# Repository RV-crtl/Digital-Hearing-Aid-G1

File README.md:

# G1 · Standalone adaptive hearing prototype

**STM32L476RG · custom KiCad PCB · FreeRTOS · microphone / Bluetooth / induction-loop audio · physical controls**

## Start with the R26.10 code walkthrough

**[Open the four-subsystem execution guide](Documentation/SUBSYSTEMS/README.md)** — follow the real startup-to-sound runtime flow, then dive into a member's source code:

[**Anna — controls**](Documentation/SUBSYSTEMS/ANNA_CONTROLS.md) · [**Ryan — BT/telecoil**](Documentation/SUBSYSTEMS/RYAN_CONNECTIVITY.md) · [**Mariya — microphone/DSP**](Documentation/SUBSYSTEMS/MARIYA_AUDIO_DSP.md) · [**Naomi — speaker output**](Documentation/SUBSYSTEMS/NAOMI_OUTPUT.md) · [**Interface contracts**](Documentation/SUBSYSTEMS/INTERFACES.md)

Each guide starts at the event that triggers its functions, shows annotated source excerpts and exact file paths, and traces the next task, queue, interrupt, hardware or team subsystem. The [original 39-event system execution guide](Documentation/FIRMWARE_EXECUTION_GUIDE_R26.md) remains available for the full chronological walkthrough. **Documentation baseline:** latest separately delivered QR261104.10 ZIP; repository firmware sources have not yet been synchronized to that release.

The diagram above represents real interfaces and task ownership, not fictional mechanical CAD or hardware measurements.

[**Explore the interactive website**](https://rv-crtl.github.io/Digital-Hearing-Aid-G1/) · [System architecture](Documentation/PRINTABLE_SYSTEM_DIAGRAM.md) · [Black-box demonstration plan](Documentation/BLACK_BOX_TEST_PLAN.md) · [Current evidence and requirements](Documentation/G1_CURRENT_SYSTEM_REQUIREMENTS.md) · [Hardware/KiCad](Hardware/README.md)

> **Prototype, not a certified hearing aid.** This repository contains original PCB design, software source, testing infrastructure and student-team engineering work. The maximum acoustic output has not been independently calibrated for use on or in the ear. Public access is not a general reuse licence; see [publication and contributor rights](Documentation/PUBLICATION_GATE.md).

## Firmware navigation and STM32CubeIDE import

**[Read the R26 boot-to-speaker function walkthrough](Documentation/FIRMWARE_EXECUTION_GUIDE_R26.md)** — chronological annotated code excerpts, physical hardware paths, per-source DSP functions, peripheral drivers, source routing, FreeRTOS tasks, speaker FIFO, diagnostics, and exact `Core/Src/` locations.

To download a **firmware-only ZIP from GitHub**, open [Actions → Export clean STM32CubeIDE project](../../actions/workflows/cubeide-clean-export.yml), choose **Run workflow**, and download the `STM32CubeIDE-clean-project` artifact from the completed run. Alternatively run `Tools/Export-CubeIDE.ps1 -OutputPath dist` in PowerShell from the repository checkout. These exports reflect the **repository revision being built**, not the separate QR261104.8 ZIP until the source-sync issue below is resolved.

For a source checkout, use **File → Import → Existing Projects into Workspace** and select the repository root containing `.project` and `.cproject`; do not import a historical reference firmware as a second project. The active application entry point is **`Core/Src/main.c`**, and the development configuration is described by the root `.ioc`. Commit history retains deleted recovery/prototype files if historical investigation is needed.

**Release synchronization:** to publish the supplied QR261104.8 ZIP into a local Git clone safely, use [`Tools/Sync-FirmwareRelease.ps1`](Tools/Sync-FirmwareRelease.ps1). Run it first with `-ZipPath <path-to-ZIP>` for validation and again with `-Apply` to replace the active firmware, create a Git commit and push to `main`. It requires a clean clone and your existing GitHub Git credentials. The QR261104.8 clean firmware archive distributed separately contains newer telecoil modules than the current repository revision. This repository should not be represented as the exact QR261104.8 release until its source and `.ioc` are synchronized and a native CubeIDE build passes. The guide describes QR261104.8 and marks differences where relevant.

## The real prototype

The physical target is a **standalone custom PCB**, not a Nucleo board. A ST-LINK is needed only for programming and optional engineering diagnosis, not for intended normal operation. The hardware incorporates an STM32L476RG, digital PDM microphone, MPR121 capacitive touch, rotary encoder, Bluetooth audio, a telecoil input with PCM1808 conversion, FreeRTOS and a speaker/audio-output chain. The bench-tested R24 firmware was reported to operate without Nucleo after a wiring issue was resolved.

The team subsequently developed **R26** with higher-sensitivity ambient audio, telecoil idle-noise reduction, adaptive gain, and incremental acoustic feature clustering. **R26 firmware is a candidate, not a confirmed on-PCB acceptance result.**

| Function | Evidence currently available | Important qualification |
| --- | --- | --- |
| Microphone → speaker | Operator-confirmed in R24; R26 DSP host tests | Distant pickup, distortion, safe SPL and ambient balance need measurement |
| Bluetooth → speaker | Operator-confirmed in R24 | Bluetooth module and source output remain subject to demonstration checks |
| Telecoil → speaker | Operator-confirmed with **PCM LOW16** and **FILTER ON** | Residual analogue hiss/weak-signal behaviour needs listening and bench measurements |
| MPR121 touch / encoder | Operator-confirmed, R21 control regression tests | Repeatability and user-response timing remain black-box criteria |
| Untethered USB-C power | R24 operator-confirmed after resolving external wiring | Battery source/protection/charging cannot be inferred from this result |
| Adaptive scene model | R26 portable C tests | **Three unsupervised clusters**, not a pretrained speech/car/pedestrian classifier |
| FreeRTOS / DMA | Static contracts and host tests | Final CPU load, timing, interrupts, underruns and SRAM headroom need recorded board evidence |

## Important: two firmware baselines

**Do not flash the root CubeIDE project assuming it is R26.** The root files currently include an earlier Nucleo-oriented group source baseline, augmented with portable R20–R26 DSP/control improvements. R26's complete custom-PCB project was distributed separately; a clean, native STM32CubeIDE 1.19.0 GCC build and intentional whole-project promotion are required before declaring it this repository's authoritative firmware. The runtime should not be assembled by casually combining half of one firmware revision with the other.

See [firmware integration and source ownership](Documentation/G1_CURRENT_SYSTEM_REQUIREMENTS.md) and [integration issue #27](https://github.com/RV-crtl/Digital-Hearing-Aid-G1/issues/27).

## Interactive engineering site

The [site](https://rv-crtl.github.io/Digital-Hearing-Aid-G1/) provides an interactive CAD explorer (3MF/GLB with local upload), source-linked **original KiCad schematics**, signal paths and task ownership, code references, and a demonstration checklist. All files under `Hardware/Original_KiCad/` remain unchanged.

The uploaded **November 2026 full multi-body assembly** contains 1,713 3MF mesh objects (460,021 triangles), including PCB, housing and separated structures. The *previous* 3MF stored at `docs/assets/g1-assembly.3mf` is an earlier revision. The newest upload can be opened through the site's **Open your 3D CAD** control without sending it to a server; its full binary is not yet tracked on GitHub. See [CAD provenance and viewing guide](Documentation/CAD_ASSEMBLY_AND_VIEWERS.md).

## Project navigation

| Area | Start here |
| --- | --- |
| Software / RTOS | [Core source](Core/Src) · [source ownership map](Documentation/CODE_MAP.md) |
| DSP and adaptive learning | [Ambient DSP](Core/Src/g1_ambient_dsp.c) · [online clusters](Core/Src/g1_scene_ml.c) · [telecoil cleanup](Core/Src/tc_cleanup.c) |
| Circuits / layout | [Original KiCad files](Hardware/Original_KiCad) · [hardware notes](Hardware/README.md) |
| Firmware import | [CubeIDE procedure](Documentation/GROUP_G1_IMPORT_AND_BUILD.md) · [R26 integration gate](https://github.com/RV-crtl/Digital-Hearing-Aid-G1/issues/27) |
| Demonstration | [System diagram](Documentation/PRINTABLE_SYSTEM_DIAGRAM.md) · [current requirements](Documentation/G1_CURRENT_SYSTEM_REQUIREMENTS.md) · [20-minute black-box test](Documentation/BLACK_BOX_TEST_PLAN.md) |
| Validation / CI | [Host validation](Validation/README.md) · [Actions](https://github.com/RV-crtl/Digital-Hearing-Aid-G1/actions) |
| Contributors / release | [CONTRIBUTING](CONTRIBUTING.md) · [SECURITY](SECURITY.md) · [publication gate](Documentation/PUBLICATION_GATE.md) |

## Working practices

Run `python3 Validation/run_host_validation.py`, `python3 docs/validate_site.py` and the relevant portable C tests before submitting a PR. **Green source-level CI does not mean ARM firmware compiled, a device booted, or acoustic performance was measured.** The correct demonstration image must start from its intended regulated power supply with ST-LINK and diagnostics disconnected; no synthetic stress/demo tasks should be enabled for operating mode.

Earlier G2/G3/G5/G11 and R-series materials remain in `Documentation/` for traceability, but **the current requirements and black-box plan linked above supersede their historical demonstration descriptions.** Avoid presenting historical statements about an unintegrated mic, Nucleo B1, or simulated user controls as the current PCB's features.

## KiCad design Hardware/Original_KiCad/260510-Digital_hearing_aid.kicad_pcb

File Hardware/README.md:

# KiCad electrical hardware — actual supplied group design

Open [`Original_KiCad/260510-Digital_hearing_aid.kicad_pro`](Original_KiCad/260510-Digital_hearing_aid.kicad_pro) using KiCad's **Project Manager** (rather than separately opening the board and schematics). PCB and hierarchical schematic pages are included. The board is **NOT validated/fabrication-approved** by inclusion in GitHub.

## Critical editing dependency

`fp-lib-table` and `sym-lib-table` reference numerous `${KIPRJMOD}/...` third-party symbol and footprint library folders. Several were supplied in the original group design ZIP but were not copied into this code repository. KiCad can often *view* embedded schematic symbol and PCB footprint representations, but library reassignment and full schematic/PCB editing may fail. Obtain the group's original `260802-Digital_hearing_aid_w_PCB` archive and copy only approved/licensed dependencies into `Hardware/Original_KiCad/`, preserving relative paths. Keep vendor library notices and provenance. Do **not** commit the original archive's `.git`, `.history`, caches, thousands of unrelated components or unreviewed third-party binaries.

Run:

```bash
python3 Validation/python/audit_kicad.py
```

It enumerates unresolved library path references, project/schematic presence and basic PCB object counts. **It does not run KiCad ERC or DRC**.

## Actual required electrical checks

1. Confirm net/pin assignment using [`STM32_U13_PINMAP.csv`](STM32_U13_PINMAP.csv) and the schematic, especially different STM32 peripheral alternate functions compared with the Nucleo firmware.
2. Run KiCad schematic ERC and PCB DRC in a compatible KiCad installation and attach *unedited reports* with the tool version and rule configuration.
3. Verify power input path / source selection, regulated rails, analogue ground, USB-C CC resistors, ESD, debug connector, HSE, BOOT0 and RESET.
4. Confirm the unconnected MPR121 address/IRQ and encoder push contacts. Don't claim these work without design corrections and testing.
5. Check that no 2-cell LiFePO4 charge/balance stage is falsely implied by the USB-C connector.
6. Fabricate only after manufacturer stack-up checks, Gerber review, DFM and real continuity/power-up tests.

For the risk and peripheral porting checklist see [`CUSTOM_PCB_PORTING_CHECKLIST.md`](CUSTOM_PCB_PORTING_CHECKLIST.md).

## G11 intended operating supply and standalone target

The team specifies **two 26650 LiFePO4 3.25 V nominal cells in series** (6.50 V nominal). This value is the **battery pack**, not the MCU supply rail: trace the actual cell balancing/protection, current limiting, low-voltage cutoff, buck/LDO conversion and acoustic output stages before operating. The final demonstrator is the custom PCB alone: it must not depend on a Nucleo, debug dongle, PC or serial console. The team reports physical hardware operational, but a specific firmware SHA/PCB revision/end-to-end black-box test record is not attached here. See [G11 custom-PCB bring-up plan](../Documentation/G11_STANDALONE_CUSTOM_PCB_RELEASE_PLAN.md).

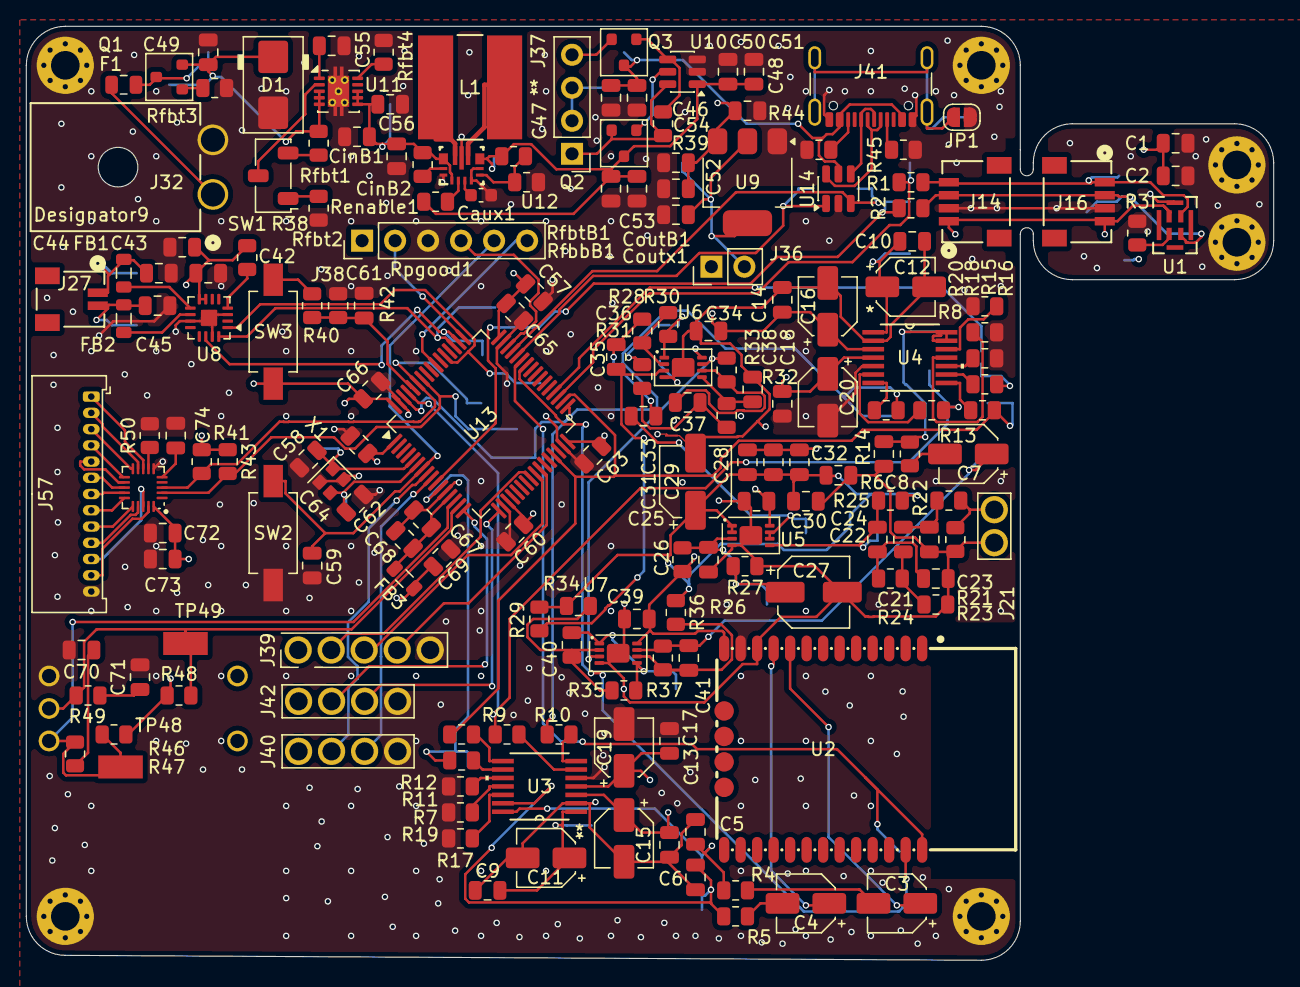
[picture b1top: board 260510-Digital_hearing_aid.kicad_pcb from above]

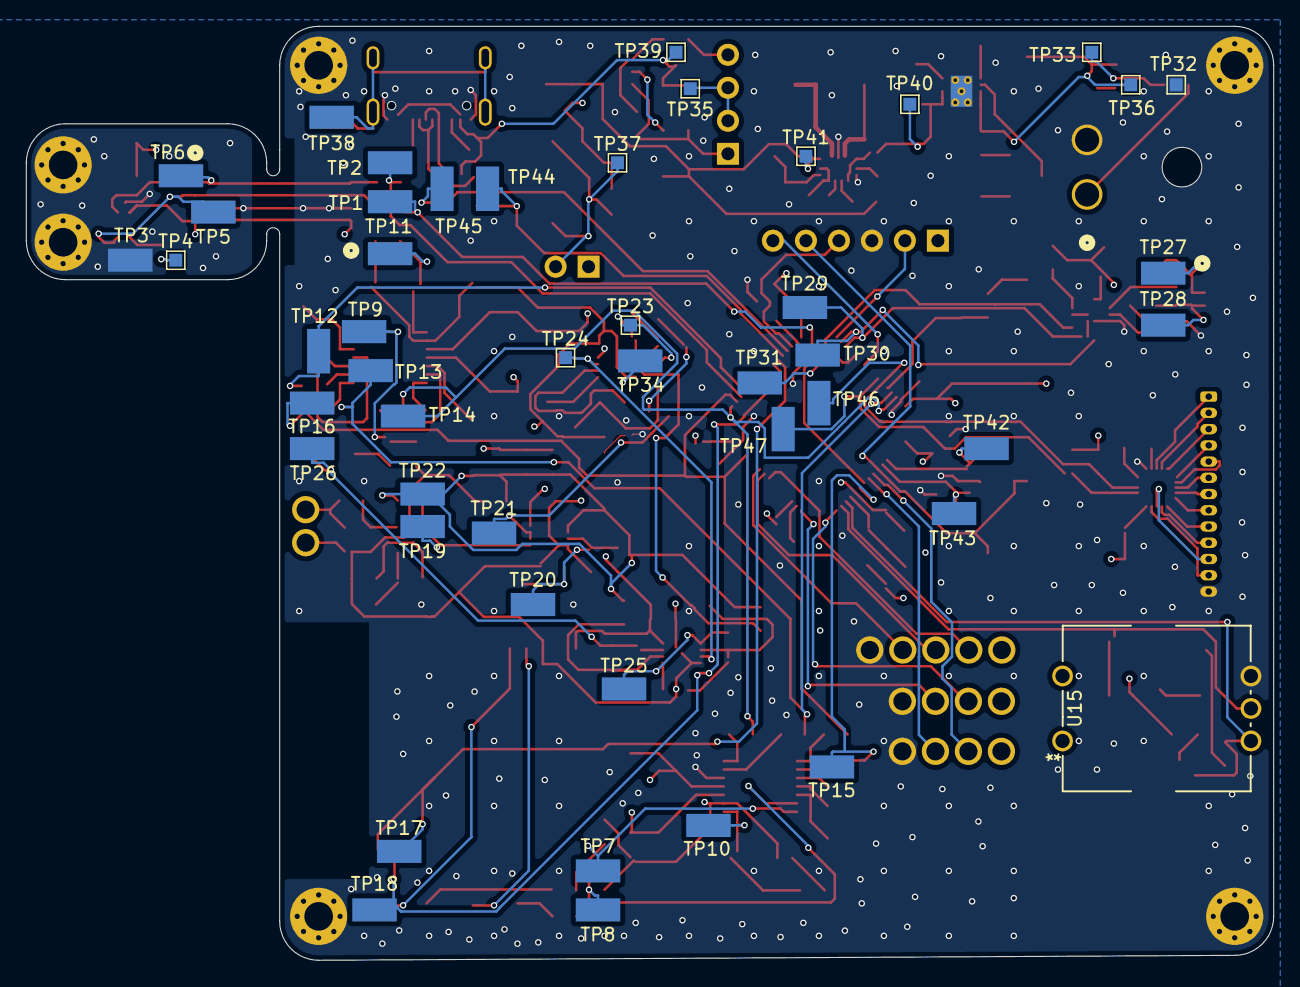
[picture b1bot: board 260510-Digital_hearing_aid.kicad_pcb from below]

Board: 4 copper layers, 96.0 x 71.9 mm, 236 parts (48 on the bottom side), 134 nets.

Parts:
C1, C42, C46, C50, C57: 10u; C_0805_2012Metric
C2, C9, C10, C13, C14, C17, C18, C25, C26, C28, C30, C31, C32, C33, C34, C39, C43, C47, C49, C51, C54, C59, C60, C61, C63, C64, C65, C66, C72, C73, C74: 100n; C_0805_2012Metric
C3, C4, C7, C11, C12, C15, C16, C19, C20: 10u; CP_Elec_4x5.3
C5, C6, C8: 100p; C_0805_2012Metric
C21, C44, C45: 470p; C_0805_2012Metric
C22: 33n; C_0805_2012Metric
C23, C55: 1n; C_0805_2012Metric
C24, C56, C68, C69: 1u; C_0805_2012Metric
C27, C29: 10u; CP_Elec_5x5.7
C35, C36: 22n; C_0805_2012Metric
C37: 3n; C_0805_2012Metric
C38: 1n5; C_0805_2012Metric
C40, C41: 22p; C_0805_2012Metric
C48, C52: 22u; C_0805_2012Metric
C53: 47u; C_0805_2012Metric
C58, C62: 10p; C_0805_2012Metric
C67, C70, C71: 10n; C_0805_2012Metric
Caux1: 100n; C_0603_1608Metric
CinB1, CinB2: 22u; C_0805_2012Metric
CoutB1: 22u; C_0805_2012Metric
Coutx1: 10u; C_0805_2012Metric
D1: SMBJ8.0A; D_SMB
F1: Fuse; Fuse_0805_2012Metric
FB1, FB2, FB3: 120R @100MHz; L_0805_2012Metric
H1, H2, H3, H4, H5, H6: MountingHole_Pad; MountingHole_2.2mm_M2_Pad_Via
J14, J16: Microphone Connectors; CONN_SM04B-SRSS-TB_JST
J21: Telecoil; PinHeader_01x02_P2.54mm_Vertical_THT_D1.4mm
J27: Bone Conductor Connector; CONN_SM02B-SRSS-TB_JST
J32: 1726480102; CONN_SD-172648-0000_02_MOL
J36: Conn_01x02_Pin; PinHeader_1x02_P2.54mm_Vertical
J37: Conn_01x04_Pin; PinHeader_1x04_P2.54mm_Vertical
J38: ST_LINK; PinHeader_1x06_P2.54mm_Vertical
J39: Number of Lines; PinHeader_01x05_P2.54mm_Vertical_THT_D1.4mm
J40, J42: Impedance @ Frequency; PinHeader_01x04_P2.54mm_Vertical_THT_D1.4mm
J41: USB_C_Receptacle_USB2.0_16P; USB_C_Receptacle_GCT_USB4105-xx-A_16P_TopMnt_Horizontal
J57: Conn_01x13; Molex_PicoBlade_53048-1310_1x13_P1.25mm_Horizontal
JP1: SolderJumper_2_Open; SolderJumper-2_P1.3mm_Open_RoundedPad1.0x1.5mm
L1: 1u5; IND_BOURNS_SDR0805
NT1: NetTie_2; Net_Tie_0.16mm_6mil
Q1, Q2, Q3: AO3419; SOT-23
R1, R2, R30, R33: 33R; R_0805_2012Metric
R3, R4, R5, R6, R7, R8, R17, R18, R19, R20, R24, R34, R36, R40, R41, R43, R46, R47, R48, R49: 10k; R_0805_2012Metric
R9, R10, R11, R12, R13, R14, R15, R16: 100R; R_0805_2012Metric
R21, R25, R38: 100k; R_0805_2012Metric
R22: 1k; R_0805_2012Metric
R23, R35, R37: 47k; R_0805_2012Metric
R26, R27: 22k; R_0805_2012Metric
R28: 21k5; R_0805_2012Metric
R29: 43k; R_0805_2012Metric
R31, R32: 11k7; R_0805_2012Metric
R39: 470k; R_0805_2012Metric
R42: 220R; R_0805_2012Metric
R44, R45: 5k1; R_0805_2012Metric
R50: 75k; R_0805_2012Metric
Renable1: 10k; R_0805_2012Metric
RfbbB1: 100k; R_0805_2012Metric
Rfbt1: 301k; R_0805_2012Metric
Rfbt2, Rfbt3: 100k; R_0805_2012Metric
Rfbt4: 45k3; R_0805_2012Metric
RfbtB1: 523k; R_0805_2012Metric
Rpgood1: 100k; R_0805_2012Metric
SW1: SW_Nidec_CAS-120TA; Nidec_Copal_CAS-120A
SW2, SW3: Switch_Tactile_CnK; Button_CnK_PTS636.0_6x3.5mm
TP1: MicClk1; KEYSTONE_5015
TP2: MicSd1; KEYSTONE_5015
TP3: GND1; KEYSTONE_5015
TP4: Ext3V0; TestPoint_Pad_1.0x1.0mm
TP5: MicClk2; KEYSTONE_5015
TP6: MicSd2; KEYSTONE_5015
TP7: VinR1; KEYSTONE_5015
TP8: VinL1; KEYSTONE_5015
TP9: TcVin1; KEYSTONE_5015
TP10: BtVref_adc1; KEYSTONE_5015
TP11: TcVref_adc1; KEYSTONE_5015
TP12: Sai2SD1; KEYSTONE_5015
TP13: SaiMCLK1; KEYSTONE_5015
TP14: SaiFS1; KEYSTONE_5015
TP15: SaiSD1; KEYSTONE_5015
TP16: SaiSCK1; KEYSTONE_5015
TP17: BtRx1; KEYSTONE_5015
TP18: BtTx1; KEYSTONE_5015
TP19: BuffIn1; KEYSTONE_5015
TP20: Buff+1; KEYSTONE_5015
TP21: BuffOut1; KEYSTONE_5015
TP22: TcVref1; KEYSTONE_5015
TP23: FiltIn1; TestPoint_Pad_1.0x1.0mm
TP24: FiltOut1; TestPoint_Pad_1.0x1.0mm
TP25: TcAmpIn1; KEYSTONE_5015
TP26: TcAmpOut1; KEYSTONE_5015
TP27: Spk+1; KEYSTONE_5015
TP28: Spk-1; KEYSTONE_5015
TP29: SpkCK1; KEYSTONE_5015
TP30: SpkFS1; KEYSTONE_5015
TP31: SpkSD1; KEYSTONE_5015
TP32: BATT-; TestPoint_Pad_1.0x1.0mm
TP33: BATT+; TestPoint_Pad_1.0x1.0mm
TP34: GndA1; KEYSTONE_5015
TP35: 5V; TestPoint_Pad_1.0x1.0mm
TP36: TpsVin1; TestPoint_Pad_1.0x1.0mm
TP37: 3V0; TestPoint_Pad_1.0x1.0mm
TP38: ChassGnd1; KEYSTONE_5015
TP39: VBus1; TestPoint_Pad_1.0x1.0mm
TP40: TpsOut1; TestPoint_Pad_1.0x1.0mm
TP41: BATT5V+1; TestPoint_Pad_1.0x1.0mm
TP42: HseIN1; KEYSTONE_5015
TP43: HseOUT1; KEYSTONE_5015
TP44: UsbD-1; KEYSTONE_5015
TP45: UsbD+1; KEYSTONE_5015
TP46: CaptoSDA1; KEYSTONE_5015
TP47: CaptoSCL1; KEYSTONE_5015
TP48: EncA1; KEYSTONE_5015
TP49: EncB1; KEYSTONE_5015
U1: MP34DT05TR-A; MP34DT05TR-A_STM
U2: DFR0781; COMM-SMD_L23.0-W15.5-P1.27_DFR0781
U3, U4: PCM1808PWR; PW14
U5, U6, U7: MCP6232T-E-MNY; DFN-8-1EP_3x2mm_P0.5mm_EP1.75x1.45mm
U8: MAX98357A; TQFN-16-1EP_3x3mm_P0.5mm_EP1.23x1.23mm
U9: AMS1117-3.3; SOT-223-3_TabPin2
U10: LTC4412ES6#TRMPBF; TSOT-23-6
U11: TPS259260DRCR; VSON-10_Custom
U12: TPS63070RNMR; RNM0015A
U13: STM32L476RGTx; LQFP-64_10x10mm_P0.5mm
U14: USBLC6-2SC6; SOT-23-6
U15: PEC11R-4215F-S0024; TO_215F-S0024
U16: MPR121QR2; QFN-20_3x3mm_P0.4mm
X1: 16MHz; Crystal_SMD_SeikoEpson_FA128-4Pin_2.0x1.6mm

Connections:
3.3V_A: C67.1, C68.1, FB3.1, U13.13 (VDDA)
+3V3: C1.1, C2.1, C17.1, C18.1, C19.1, C20.1, C57.1, C60.1, C63.1, C64.1, C65.1, C66.1, C69.1, C72.1, C73.2, FB3.2, J14.1, J16.4, J36.1, J38.1, J39.1, J40.1, J42.1, R41.1, R43.1, SW3.2, TP4.1 (1_1), U1.1 (VDD), U3.4 (VDD), U4.4 (VDD), U13.1 (VBAT), U13.19 (VDD), U13.32 (VDD), U13.48 (VDDUSB), U13.64 (VDD), U16.20 (VDD)
+5V: C13.1, C14.1, C15.1, C16.1, C25.1, C34.1, C39.1, C42.1, C43.1, C48.2, C53.1, C54.2, J37.2, J37.3, R26.2, R38.1, R46.1, R48.1, TP35.1 (1_1), U2.13 (VCC), U3.3 (VCC), U4.3 (VCC), U5.8 (V+), U6.8 (V+), U7.8 (V+), U8.7 (VDD), U8.8 (VDD), U9.3 (VI)
+5VBAT: C50.1, C51.2, CoutB1.1, Coutx1.1, Q2.3 (D), RfbtB1.1, Rpgood1.1, TP41.1 (1_1), U10.1 (VIN), U12.7 (VOUT), U12.8 (VOUT)
/Control, Connectivity, and Power/Audio Input/DFSDM_CLK: J14.3, J16.2, R2.2, TP5.TP, U1.3 (CLK)
/Control, Connectivity, and Power/Audio Input/DFSDM_DOUT: J14.4, J16.1, R1.2, TP6.TP, U1.4 (DOUT)
/Control, Connectivity, and Power/Audio Input/DFSDM_MIC.CKOUT: R2.1, TP1.TP, U13.10 (DFSDM1_CKOUT)
/Control, Connectivity, and Power/Audio Input/DFSDM_MIC.SD: R1.1, TP2.TP, U13.35 (DFSDM1_DATIN2)
/Control, Connectivity, and Power/Connectivity/Analog Frontend/Active Bandpass 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: C35.1, TP21.TP, U5.6 (-), U5.7
/Control, Connectivity, and Power/Connectivity/Analog Frontend/Active Bandpass 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: R33.1, TP24.1 (1_1), U6.7, U7.3 (+)
/Control, Connectivity, and Power/Connectivity/Analog Frontend/TC+: J21.1, R21.2, R22.2
/Control, Connectivity, and Power/Connectivity/Analog Frontend/TC_DACO: C7.1, C41.2, R37.2, TP26.TP, U7.7
/Control, Connectivity, and Power/Connectivity/Analog Frontend/Telecoil Buffer 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: C24.2, R25.2, TP19.TP, U5.5 (+)
/Control, Connectivity, and Power/Connectivity/BT_BCK: R12.1, U3.8 (BCK)
/Control, Connectivity, and Power/Connectivity/BT_DACL: C4.1, U2.10 (DACL)
/Control, Connectivity, and Power/Connectivity/BT_DACR: C3.1, U2.9 (DACR)
/Control, Connectivity, and Power/Connectivity/BT_DOUT: R11.1, U3.9 (DOUT)
/Control, Connectivity, and Power/Connectivity/BT_FMT: R17.1, U3.12 (FMT)
/Control, Connectivity, and Power/Connectivity/BT_LRCK: R10.1, U3.7 (LRCK)
/Control, Connectivity, and Power/Connectivity/BT_MD0: R7.1, U3.10 (MD0)
/Control, Connectivity, and Power/Connectivity/BT_MD1: R19.1, U3.11 (MD1)
/Control, Connectivity, and Power/Connectivity/BT_SCKI: R9.1, U3.6 (SCKI)
/Control, Connectivity, and Power/Connectivity/BT_VINL: C6.1, R5.2, TP8.TP, U3.13 (VINL)
/Control, Connectivity, and Power/Connectivity/BT_VINR: C5.1, R4.2, TP7.TP, U3.14 (VINR)
/Control, Connectivity, and Power/Connectivity/BT_VREF: C9.1, C11.1, TP10.TP, U3.1 (VREF)
/Control, Connectivity, and Power/Connectivity/SAI1A_CONN.FS: R10.2, R14.2, TP14.TP, U13.33 (SAI2_FS_A), U13.62 (SAI1_FS_A)
/Control, Connectivity, and Power/Connectivity/SAI1A_CONN.MCLK: R9.2, R13.2, TP13.TP, U13.61 (SAI1_MCLK_A)
/Control, Connectivity, and Power/Connectivity/SAI1A_CONN.SCK: R12.2, R16.2, TP16.TP, U13.29 (SAI1_SCK_A), U13.34 (SAI2_SCK_A)
/Control, Connectivity, and Power/Connectivity/SAI1A_CONN.SD: R11.2, TP15.TP, U13.11 (SAI1_SD_A)
/Control, Connectivity, and Power/Connectivity/SAI_CONN_SD: R15.2, TP12.TP, U13.36 (SAI2_SD_A)
/Control, Connectivity, and Power/Connectivity/TC_BCK: R16.1, U4.8 (BCK)
/Control, Connectivity, and Power/Connectivity/TC_DOUT: R15.1, U4.9 (DOUT)
/Control, Connectivity, and Power/Connectivity/TC_FMT: R18.1, U4.12 (FMT)
/Control, Connectivity, and Power/Connectivity/TC_LRCK: R14.1, U4.7 (LRCK)
/Control, Connectivity, and Power/Connectivity/TC_MD0: R8.1, U4.10 (MD0)
/Control, Connectivity, and Power/Connectivity/TC_MD1: R20.1, U4.11 (MD1)
/Control, Connectivity, and Power/Connectivity/TC_SCKI: R13.1, U4.6 (SCKI)
/Control, Connectivity, and Power/Connectivity/TC_VIN: C8.1, R6.2, TP9.TP, U4.13 (VINL), U4.14 (VINR)
/Control, Connectivity, and Power/Connectivity/TC_VREF: C10.1, C12.1, TP11.TP, U4.1 (VREF)
/Control, Connectivity, and Power/Connectivity/UART_BT.RX: TP17.TP, U2.26 (PB0/TX), U13.43 (USART1_RX)
/Control, Connectivity, and Power/Connectivity/UART_BT.TX: TP18.TP, U2.25 (PB1/RX), U13.42 (USART1_TX)
/Control, Connectivity, and Power/Output/OUT+: FB1.1, U8.9 (OUTP)
/Control, Connectivity, and Power/Output/OUT-: FB2.1, U8.10 (OUTN)
/Control, Connectivity, and Power/Output/SAI_SPEAKER.FS: TP30.TP, U8.14 (LRCLK), U13.50 (SAI2_FS_B)
/Control, Connectivity, and Power/Output/SAI_SPEAKER.SCK: TP29.TP, U8.16 (BCLK), U13.51 (SAI2_SCK_B)
/Control, Connectivity, and Power/Output/SAI_SPEAKER.SD: TP31.TP, U8.1 (DIN), U13.53 (SAI2_SD_B)
/Control, Connectivity, and Power/Output/SPEAKER+: C44.2, FB1.2, J27.1, TP27.TP
/Control, Connectivity, and Power/Output/SPEAKER-: C45.2, FB2.2, J27.2, TP28.TP
/Control, Connectivity, and Power/Output/~SD_MODE: R38.2, U8.4 (~SD_MODE)
/Control, Connectivity, and Power/Power/EFUSE_EN: SW1.2 (B), U11.2 (EN/UVLO)
/Control, Connectivity, and Power/Power/VBATT_PROT: C49.1, D1.1 (K), Q1.2 (S), Rfbt1.1, TP36.1 (1_1), U11.3 (VIN), U11.4 (VIN), U11.5 (VIN)
/Control, Connectivity, and Power/STM32L476RG/BOOT0: C61.2, R40.1, R42.1, U13.60 (BOOT0)
/Control, Connectivity, and Power/STM32L476RG/HSE_IN: C58.1, TP42.TP, U13.5 (RCC_OSC_IN), X1.1
/Control, Connectivity, and Power/STM32L476RG/HSE_OUT: C62.2, TP43.TP, U13.6 (RCC_OSC_OUT), X1.3
/Control, Connectivity, and Power/STM32L476RG/I2C3_SCL: J40.2, U13.8 (I2C3_SCL)
/Control, Connectivity, and Power/STM32L476RG/I2C3_SDA: J40.3, U13.9 (I2C3_SDA)
/Control, Connectivity, and Power/STM32L476RG/I2C_CAPTO.SCL: R43.2, TP47.TP, U13.58 (I2C1_SCL), U16.2 (SCL)
/Control, Connectivity, and Power/STM32L476RG/I2C_CAPTO.SDA: R41.2, TP46.TP, U13.59 (I2C1_SDA), U16.3 (SDA)
/Control, Connectivity, and Power/STM32L476RG/ROTENC_OUT.A: R46.2, R47.2, TP48.TP, U13.14 (PA0), U15.A
/Control, Connectivity, and Power/STM32L476RG/ROTENC_OUT.B: R48.2, R49.2, TP49.TP, U13.15 (PA1), U15.B
/Control, Connectivity, and Power/STM32L476RG/SWCLK: J38.2, U13.49 (SYS_JTCK-SWCLK)
/Control, Connectivity, and Power/STM32L476RG/SWDIO: J38.4, U13.46 (SYS_JTMS-SWDIO)
/Control, Connectivity, and Power/STM32L476RG/SWO: J38.6, U13.55 (SYS_JTDO-SWO)
/Control, Connectivity, and Power/STM32L476RG/USART3_CK: J39.4, U13.26 (USART3_CK)
/Control, Connectivity, and Power/STM32L476RG/USART3_RX: J39.3, U13.25 (USART3_RX)
/Control, Connectivity, and Power/STM32L476RG/USART3_TX: J39.2, U13.24 (USART3_TX)
/Control, Connectivity, and Power/STM32L476RG/USART_RX: J42.3, U13.17 (USART2_RX)
/Control, Connectivity, and Power/STM32L476RG/USART_TX: J42.2, U13.16 (USART2_TX)
/Control, Connectivity, and Power/STM32L476RG/USBC_CC1: J41.A5 (CC1), R45.1
/Control, Connectivity, and Power/STM32L476RG/USBC_CC2: J41.B5 (CC2), R44.1
/Control, Connectivity, and Power/STM32L476RG/USBC_D+: J41.A6 (D+), J41.B6 (D+), U14.4 (I/O2)
/Control, Connectivity, and Power/STM32L476RG/USBC_D-: J41.A7 (D-), J41.B7 (D-), U14.6 (I/O1)
/Control, Connectivity, and Power/STM32L476RG/USB_D+: TP45.TP, U13.45 (USB_OTG_FS_DP), U14.3 (I/O2)
/Control, Connectivity, and Power/STM32L476RG/USB_D-: TP44.TP, U13.44 (USB_OTG_FS_DM), U14.1 (I/O1)
/Control, Connectivity, and Power/STM32L476RG/~RST: C59.1, J38.5, SW2.1, U13.7 (NRST)
/Control, Connectivity, and Power/User Interface/CAPTO_REXT: R50.1, U16.7 (REXT)
/Control, Connectivity, and Power/User Interface/CAPTO_VREG: C74.2, U16.5 (VREG)
Chassis GND: J41.SH (SHIELD), JP1.2 (B), TP38.TP
GND: C1.2, C2.2, C17.2, C18.2, C19.2, C20.2, C42.2, C43.2, C44.1, C45.1, C46.2, C47.1, C48.1, C49.2, C50.2, C51.1, C52.2, C53.2, C54.1, C55.2, C56.2, C57.2, C58.2, C59.2, C60.2, C61.1, C62.1, C63.2, C64.2, C65.2, C66.2, C69.2, C70.2, C71.2, C72.2, C73.1, C74.1, Caux1.2, CinB1.2, CinB2.2, CoutB1.2, Coutx1.2, D1.2 (A), H1.1 (1_1), H2.1 (1_1), H3.1 (1_1), H4.1 (1_1), H5.1 (1_1), H6.1 (1_1), J14.2, J16.3, J32.2, J38.3, J39.5, J40.4, J41.A1 (GND), J41.A12 (GND), J41.B1 (GND), J41.B12 (GND), J42.4, J57.13, JP1.1 (A), NT1.1, R3.2, R7.2, R8.2, R17.2, R18.2, R19.2, R20.2, R40.2, R44.2, R45.2, R50.2, RfbbB1.2, Rfbt2.2, Rfbt3.2, Rfbt4.2, SW2.2, TP3.TP, TP32.1 (1_1), U1.5 (GND), U2.12 (GND), U3.5 (DGND), U4.5 (DGND), U8.3 (GND), U8.11 (GND), U8.15 (GND), U8.17 (PAD), U9.1 (GND), U10.2 (GND), U10.3 (CTL), U11.11 (GND), U12.4 (GND), U12.6 (FB2), U12.10 (PGND), U12.15 (VSEL), U13.18 (VSS), U13.31 (VSS), U13.47 (VSS), U13.63 (VSS), U14.2 (GND), U15.C, U16.6 (VSS), X1.2, X1.4
GNDA: C5.2, C6.2, C8.2, C9.2, C10.2, C11.2, C12.2, C13.2, C14.2, C15.2, C16.2, C21.2, C23.2, C25.2, C26.2, C27.2, C28.2, C29.2, C30.2, C31.2, C32.2, C33.2, C34.2, C38.1, C39.2, C67.2, C68.2, J21.2, NT1.2, R21.1, R23.2, R27.1, TP34.TP, U2.11 (SGND), U3.2 (AGND), U4.2 (AGND), U5.4 (V-), U5.9 (PAD), U6.4 (V-), U6.9 (PAD), U7.4 (V-), U7.9 (PAD), U13.12 (VSSA)
unnamed: C3.2, R4.1
unnamed: C4.2, R5.1
unnamed: C7.2, R6.1
unnamed: C21.1, C22.1, R22.1
unnamed: C22.2, R23.1, R24.2
unnamed: C23.1, C24.1, R24.1
unnamed: C35.2, C36.1, R28.2
unnamed: C37.1, R31.1, R32.2
unnamed: C70.1, R47.1
unnamed: C71.1, R49.1
unnamed: F1.1, J32.1
unnamed: C52.1, J36.2, TP37.1 (1_1), U9.2 (VO)
unnamed: J37.1, Q2.2 (S), R39.1, U10.6 (SENSE)
unnamed: J37.4, Q3.2 (S)
unnamed: J57.1, U16.8 (ELE0)
unnamed: J57.2, U16.9 (ELE1)
unnamed: J57.3, U16.10 (ELE2)
unnamed: J57.4, U16.11 (ELE3)
unnamed: J57.5, U16.12 (LED0/ELE4)
unnamed: J57.6, U16.13 (LED1/ELE5)
unnamed: J57.7, U16.14 (LED2/ELE6)
unnamed: J57.8, U16.15 (LED3/ELE7)
unnamed: J57.9, U16.16 (LED4/ELE8)
unnamed: J57.10, U16.17 (LED5/ELE9)
unnamed: J57.11, U16.18 (LED6/ELE10)
unnamed: J57.12, U16.19 (LED7/ELE11)
unnamed: F1.2, Q1.3 (D), TP33.1 (1_1)
unnamed: Q1.1 (G), Rfbt3.1
unnamed: Q2.1 (G), U10.5 (GATE)
unnamed: Q3.1 (G), R39.2, U10.4 (STAT)
unnamed: R30.1, R31.2, TP23.1 (1_1), U6.1
unnamed: R42.2, SW3.1
unnamed: Rfbt1.2, SW1.3 (A)
unnamed: Rfbt2.1, SW1.1 (C)
unnamed: R3.1, U1.2 (LR)
unnamed: C26.1, C27.1, R26.1, R27.2, TP20.TP, U5.3 (+)
unnamed: C36.2, R29.2, U6.3 (+)
unnamed: R28.1, R30.2, U6.2 (-)
unnamed: C38.2, R32.1, U6.5 (+)
unnamed: C37.2, R33.2, U6.6 (-)
unnamed: C40.1, R34.2, R35.1, U7.2 (-)
unnamed: C40.2, R35.2, TP25.TP, U7.1, U7.5 (+)
unnamed: C41.1, R36.2, R37.1, U7.6 (-)
unnamed: Rfbt4.1, U11.10 (ILIM)
unnamed: C55.1, U11.1 (dV/dT)
unnamed: Renable1.2, U12.14 (EN)
unnamed: RfbbB1.1, RfbtB1.2, U12.5 (FB)
unnamed: L1.2, U12.11 (L1)
unnamed: L1.1, U12.9 (L2)
unnamed: Rpgood1.2, U12.2 (PG)
unnamed: C56.1, CinB1.1, CinB2.1, Renable1.1, TP40.1 (1_1), U11.6 (OUT), U11.7 (OUT), U11.8 (OUT), U12.1 (PS_SYNC), U12.12 (VIN), U12.13 (VIN)
unnamed: Caux1.1, U12.3 (VAUX)
TCOIL_VREF: C28.1, C29.1, C30.1, C31.1, C32.1, C33.1, R25.1, R29.1, R34.1, R36.1, TP22.TP, U5.1, U5.2 (-)
VBUS: C46.1, C47.2, J41.A4 (VBUS), J41.A9 (VBUS), J41.B4 (VBUS), J41.B9 (VBUS), Q3.3 (D), TP39.1 (1_1), U14.5 (VBUS)

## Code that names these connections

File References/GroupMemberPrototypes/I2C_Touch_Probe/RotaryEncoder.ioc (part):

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Mcu.Name=STM32L476R(C-E-G)Tx
Mcu.Package=LQFP64
Mcu.UserName=STM32L476RGTx
PA0.GPIOParameters=GPIO_PuPd,GPIO_Label,GPIO_ModeDefaultEXTI
PA0.GPIO_Label=ENC_A
PA0.GPIO_ModeDefaultEXTI=GPIO_MODE_IT_RISING_FALLING
PA0.GPIO_PuPd=GPIO_NOPULL
PA0.Signal=GPXTI0
PA1.GPIOParameters=GPIO_Label,GPIO_ModeDefaultEXTI
PA1.GPIO_Label=ENC_B
PA1.GPIO_ModeDefaultEXTI=GPIO_MODE_IT_RISING_FALLING
PA1.Signal=GPXTI1
PA12.Signal=GPIO_Input
PA13\ (JTMS-SWDIO).GPIOParameters=GPIO_Label
PA13\ (JTMS-SWDIO).GPIO_Label=TMS
PA13\ (JTMS-SWDIO).Mode=Serial_Wire
PA13\ (JTMS-SWDIO).Signal=SYS_JTMS-SWDIO
PA14\ (JTCK-SWCLK).GPIOParameters=GPIO_Label
PA14\ (JTCK-SWCLK).GPIO_Label=TCK
PA14\ (JTCK-SWCLK).Mode=Serial_Wire
PA14\ (JTCK-SWCLK).Signal=SYS_JTCK-SWCLK
PA2.GPIOParameters=GPIO_Speed,GPIO_PuPd,GPIO_Label,GPIO_Mode
PA2.GPIO_Label=USART_TX
PA2.GPIO_Mode=GPIO_MODE_AF_PP
PA2.GPIO_PuPd=GPIO_NOPULL
PA2.GPIO_Speed=GPIO_SPEED_FREQ_VERY_HIGH
PA2.Mode=Asynchronous
PA2.Signal=USART2_TX
PA3.GPIOParameters=GPIO_Speed,GPIO_PuPd,GPIO_Label,GPIO_Mode
PA3.GPIO_Label=USART_RX
PA3.GPIO_Mode=GPIO_MODE_AF_PP
PA3.GPIO_PuPd=GPIO_NOPULL
PA3.GPIO_Speed=GPIO_SPEED_FREQ_VERY_HIGH
PA3.Mode=Asynchronous
PA3.Signal=USART2_RX
PA5.GPIOParameters=GPIO_Speed,GPIO_PuPd,GPIO_Label,GPIO_ModeDefaultOutputPP
PA5.GPIO_Label=LD2 [green Led]
PA5.GPIO_ModeDefaultOutputPP=GPIO_MODE_OUTPUT_PP
PA5.GPIO_PuPd=GPIO_NOPULL
PA5.GPIO_Speed=GPIO_SPEED_FREQ_LOW
PA5.Signal=GPIO_Output
PB3\ (JTDO-TRACESWO).GPIOParameters=GPIO_Label
PB3\ (JTDO-TRACESWO).GPIO_Label=SWO
PB3\ (JTDO-TRACESWO).Signal=SYS_JTDO-SWO
PB6.Mode=I2C
PB6.Signal=I2C1_SCL
PB7.Mode=I2C
PB7.Signal=I2C1_SDA
PC13.GPIOParameters=GPIO_PuPd,GPIO_Label,GPIO_ModeDefaultEXTI
PC13.GPIO_Label=B1 [Blue PushButton]
PC13.GPIO_ModeDefaultEXTI=GPIO_MODE_IT_FALLING
PC13.GPIO_PuPd=GPIO_NOPULL
PC13.Signal=GPXTI13
PC14-OSC32_IN\ (PC14).Mode=LSE-External-Oscillator
PC14-OSC32_IN\ (PC14).Signal=RCC_OSC32_IN
PC15-OSC32_OUT\ (PC15).Mode=LSE-External-Oscillator
PC15-OSC32_OUT\ (PC15).Signal=RCC_OSC32_OUT
PH0-OSC_IN\ (PH0).Signal=RCC_OSC_IN
PH1-OSC_OUT\ (PH1).Signal=RCC_OSC_OUT
RCC.HSE_VALUE=8000000
RCC.SYSCLKFreq_VALUE=80000000
RCC.SYSCLKSource=RCC_SYSCLKSOURCE_PLLCLK
board=NUCLEO-L476RG
boardIOC=true
